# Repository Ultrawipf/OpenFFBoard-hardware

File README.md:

# OpenFFBoard-hardware
This contains the hardware designs of the OpenFFBoard

These are work in progress.
No guarantee for functionality or safety! The designs are experimental and may change at any time.
The firmware is available in the main [OpenFFBoard](https://github.com/Ultrawipf/OpenFFBoard) git.

This project requires soldering of many fine pitched parts including QFN. Availability of components may change over time so check for alternatives if something is not available.
The motor driver should be made with 2oz copper layers for best thermal performance!

The firmware may run on some third party development kits but as they have different pinouts and missing peripherals this is not recommended.

## Buy official kits
* [Elecrow](https://www.elecrow.com/open-ffboard-stm32f407-usb-interface-only.html)
* [Lectronz](https://www.lectronz.com/stores/gigawipf)
* [Tindie](https://www.tindie.com/stores/gigawipf/) or Discord.

Check the [Discord](https://discord.com/invite/gHtnEcP) and [project page](https://hackaday.io/project/163904-open-ffboard) for updates.

---

### LICENSE NOTE: The root license applies to all subfolders NOT containing their own LICENSE file. If a subfolder contains a different LICENSE file this different license applies to all subfolders below this LICENSE file.

**If you want to sell any hardware of this project yourself i would kindly ask you to get in contact with me ([mail](mailto:ffboard@y-richter.de) or Discord)**

## Changelog
### TMC Driver:

#### 1.1: (Prerelease prototype)
- Added filtering for Hall and Encoder inputs.
- Separated TMC and STM VM sense dividers

#### 1.2: (Major redesign)
- Using TMC4671-LA production version
- Added 5V buck converter
- Added emergency shutdown method by pulling enable low
- Rotated power stage. Moved all motor connectors to one side
- Moved analog encoder pins and routed differential inputs out
- Improved vcore impedance
- Increased encoder filter frequencies
- Reduced resistance of sense dividers
- Switched LM5050 to LM74700
- Space for 2 VM capacitors
- Improved mosfet protection
- Added temperature sensor pads on AGPI-B
- 50x50+100mm screw holes

#### 1.2 fix:
- Fixed silkscreen (R18 and R19 swapped)
- Modified some labels
- Added 33k gate pulldown for brake resistor
- Moved and resized vias in motor driver part (Manufacturing reliability)
- Tented vias

#### 1.2.2 (HALL):
- Redesigned power stage to use hall sensors (LEM GO SME and TMCS1100)
- Changed buffers to 74LV17APWJ
- Added opamp for TMC inputs (temperature and voltage sensing)
- Used opamp as comparator for hardware brake resistor activation point (~65V)
  
### 1.3.3:
- Analog section with separate LDO
- Support for more current sensors (ACS724)
- Optimized gate driver circuit w. resistors and diodes
- More separation between analog and power sections

### STM USB Interface:
#### 1.1:
- Initial prototype
- STM32F411RE based
- Only supports TMC4671 driver
- Only one SPI2 CS

#### 1.2:
- STM32F407VG
- Reserved PWM pins
- 3 CS pins per SPI
- CAN bus
- Reserved E-Stop
- USB Vbus sense
- separated ADCs for vsense and analog in
- LEDs moved
- Added FFBoard logo
- Changed USB diode to SMC
- Added zener pad on 5V
- Removed encoder buffer
- Higher value pwr led resistor

#### 1.2.1:
- Fixed some labels
- Moved USB socket and terminals slightly to the corners (Big usb plugs might interfere with the pins)
- Changed crystal load capacitors to lower values. (F407 DFU is very sensitive and does not work reliably with too high value caps)
- Added E-Stop capacitor against noise triggering it
- Tented vias

#### 1.2.2
- Swapped (Previously unused) Encoder Z pin from pin 65 to pin 62 because of interrupt conflicts with the DRV flag pin

#### 1.2.3
- USB-C instead of micro USB
- SPI1 uses a 2 row header
- Additional USB protections

#### 1.2.4
- Moved EXT header slightly
- Used 2 extra jumper pins for CAN termination instead of solderjumper

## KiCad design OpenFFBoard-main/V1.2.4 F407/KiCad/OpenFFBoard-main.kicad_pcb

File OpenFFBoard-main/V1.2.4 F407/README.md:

### FFBoard main USB interface F407VG
This is the heart of the Open FFBoard.
It runs the FFBoard firmware and interfaces with all your peripherals and motor drivers.

V1.2.3 and 1.2.4 is a USB-C version and adds additional USB protections.
The SPI1 port layout had to change to 2 rows instead of 1.

#### How to order yourself
You can order this board directly via [jlcpcb.com](https://jlcpcb.com/?from=Gigawipf).

The BOM and component placement files are available in the JLC assembly folder and already formatted with matching LCSC part numbers.

Everything apart from the headers can be directly assembled by JLC including the USB socket.

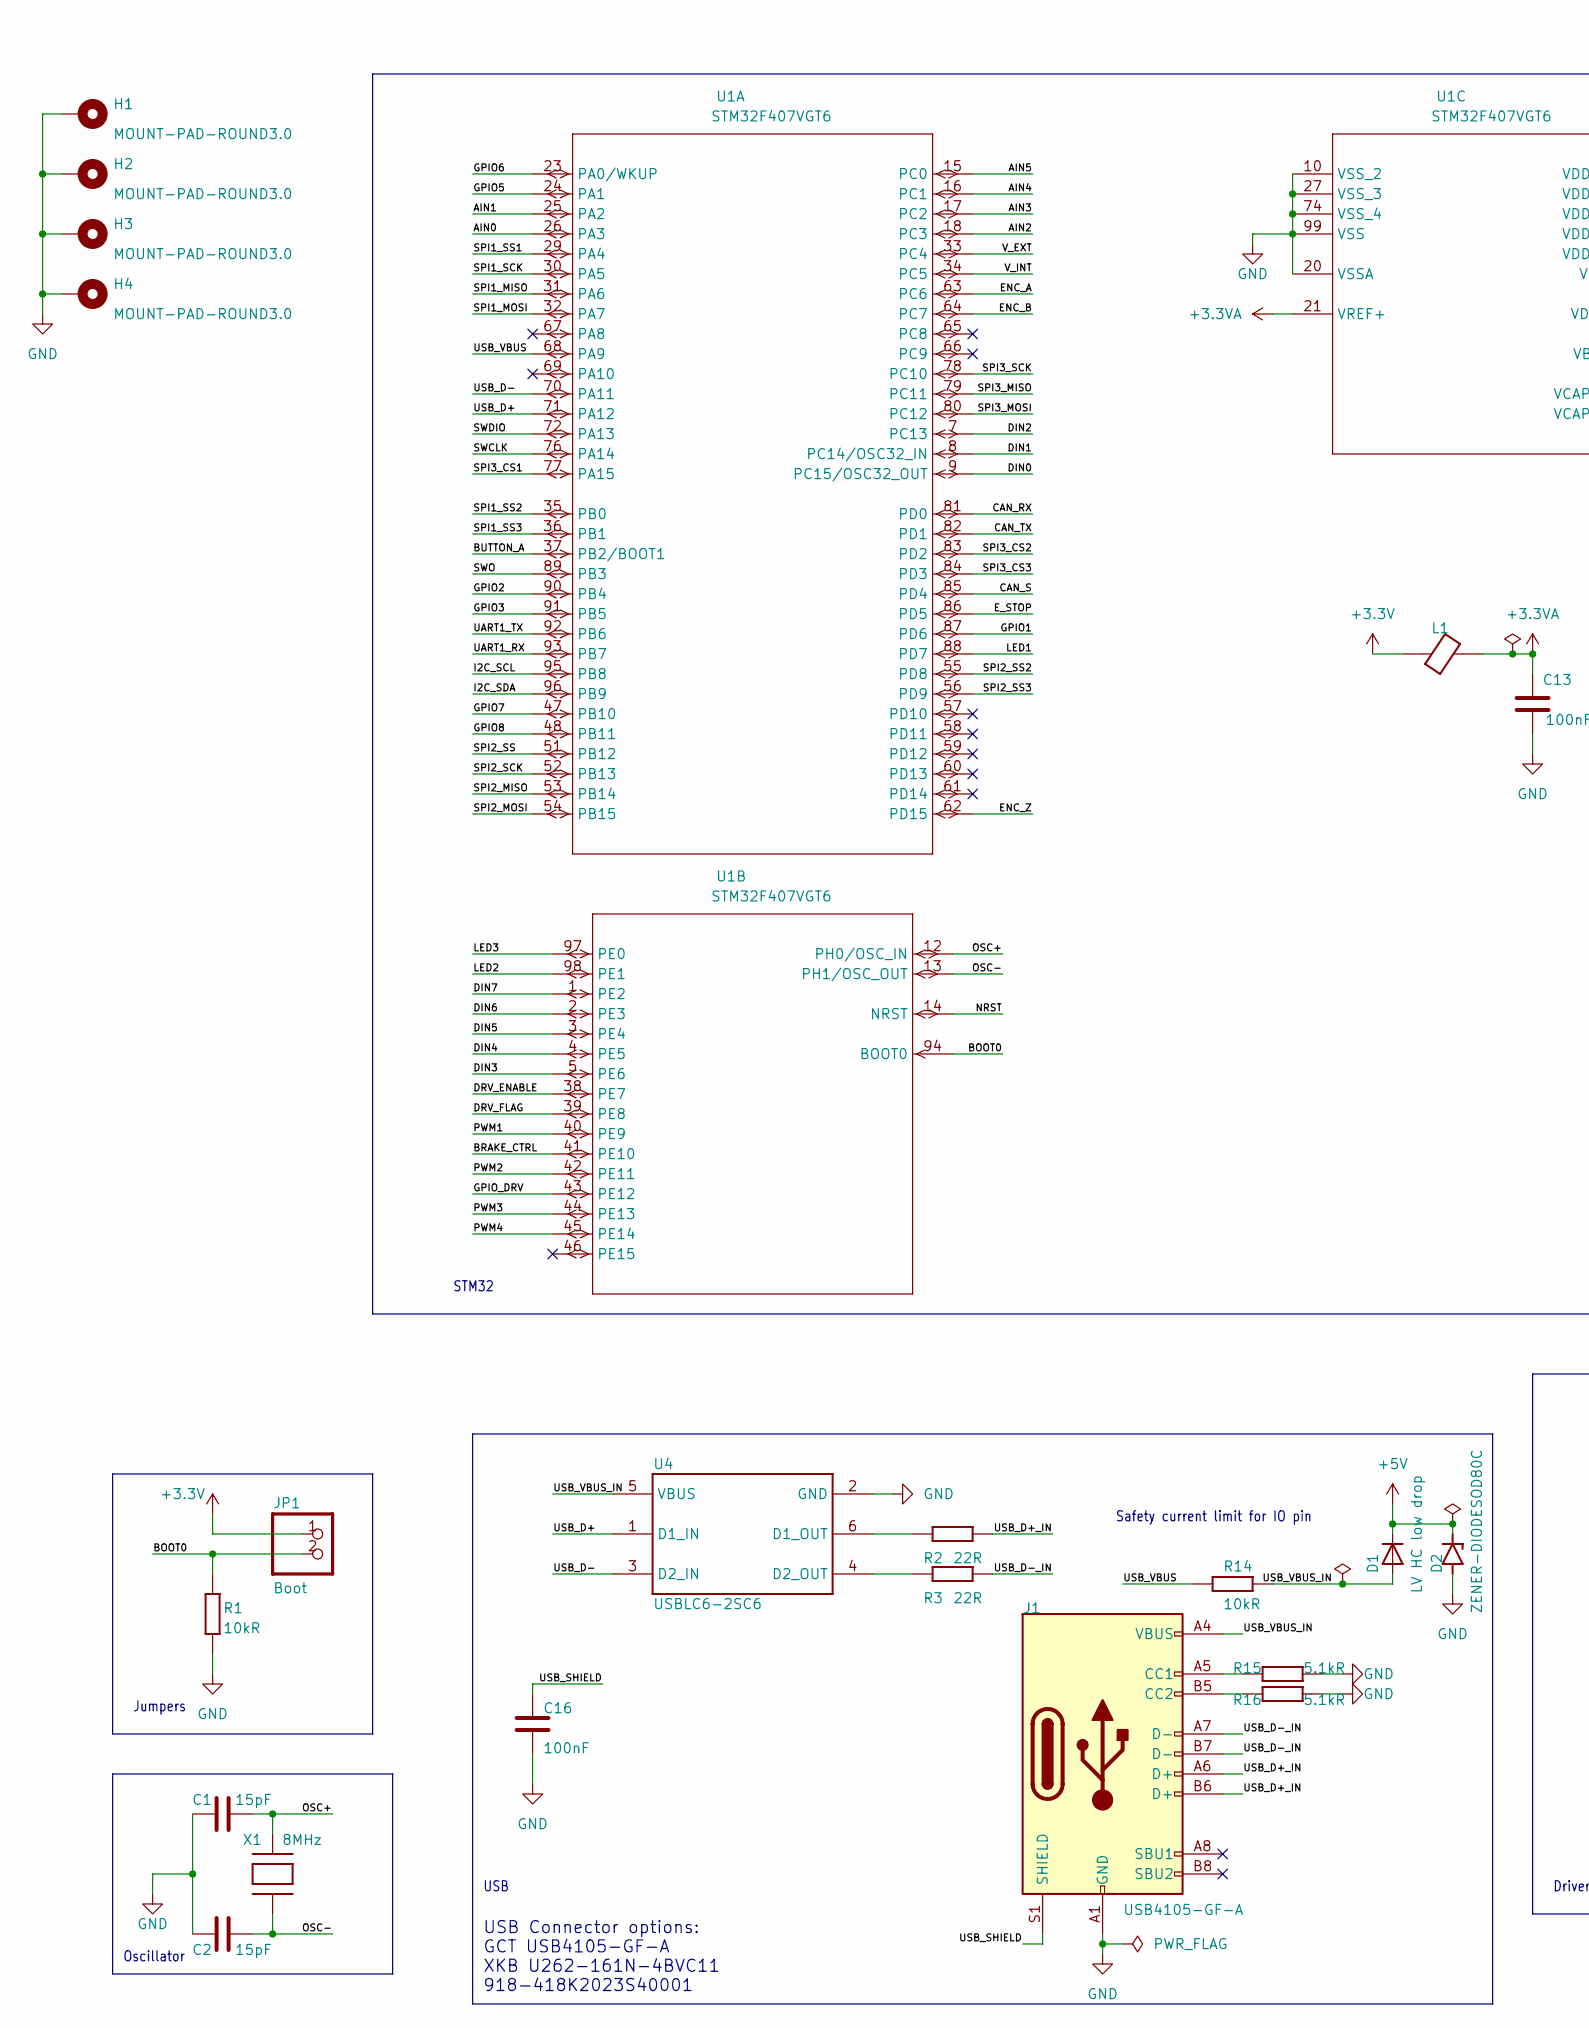
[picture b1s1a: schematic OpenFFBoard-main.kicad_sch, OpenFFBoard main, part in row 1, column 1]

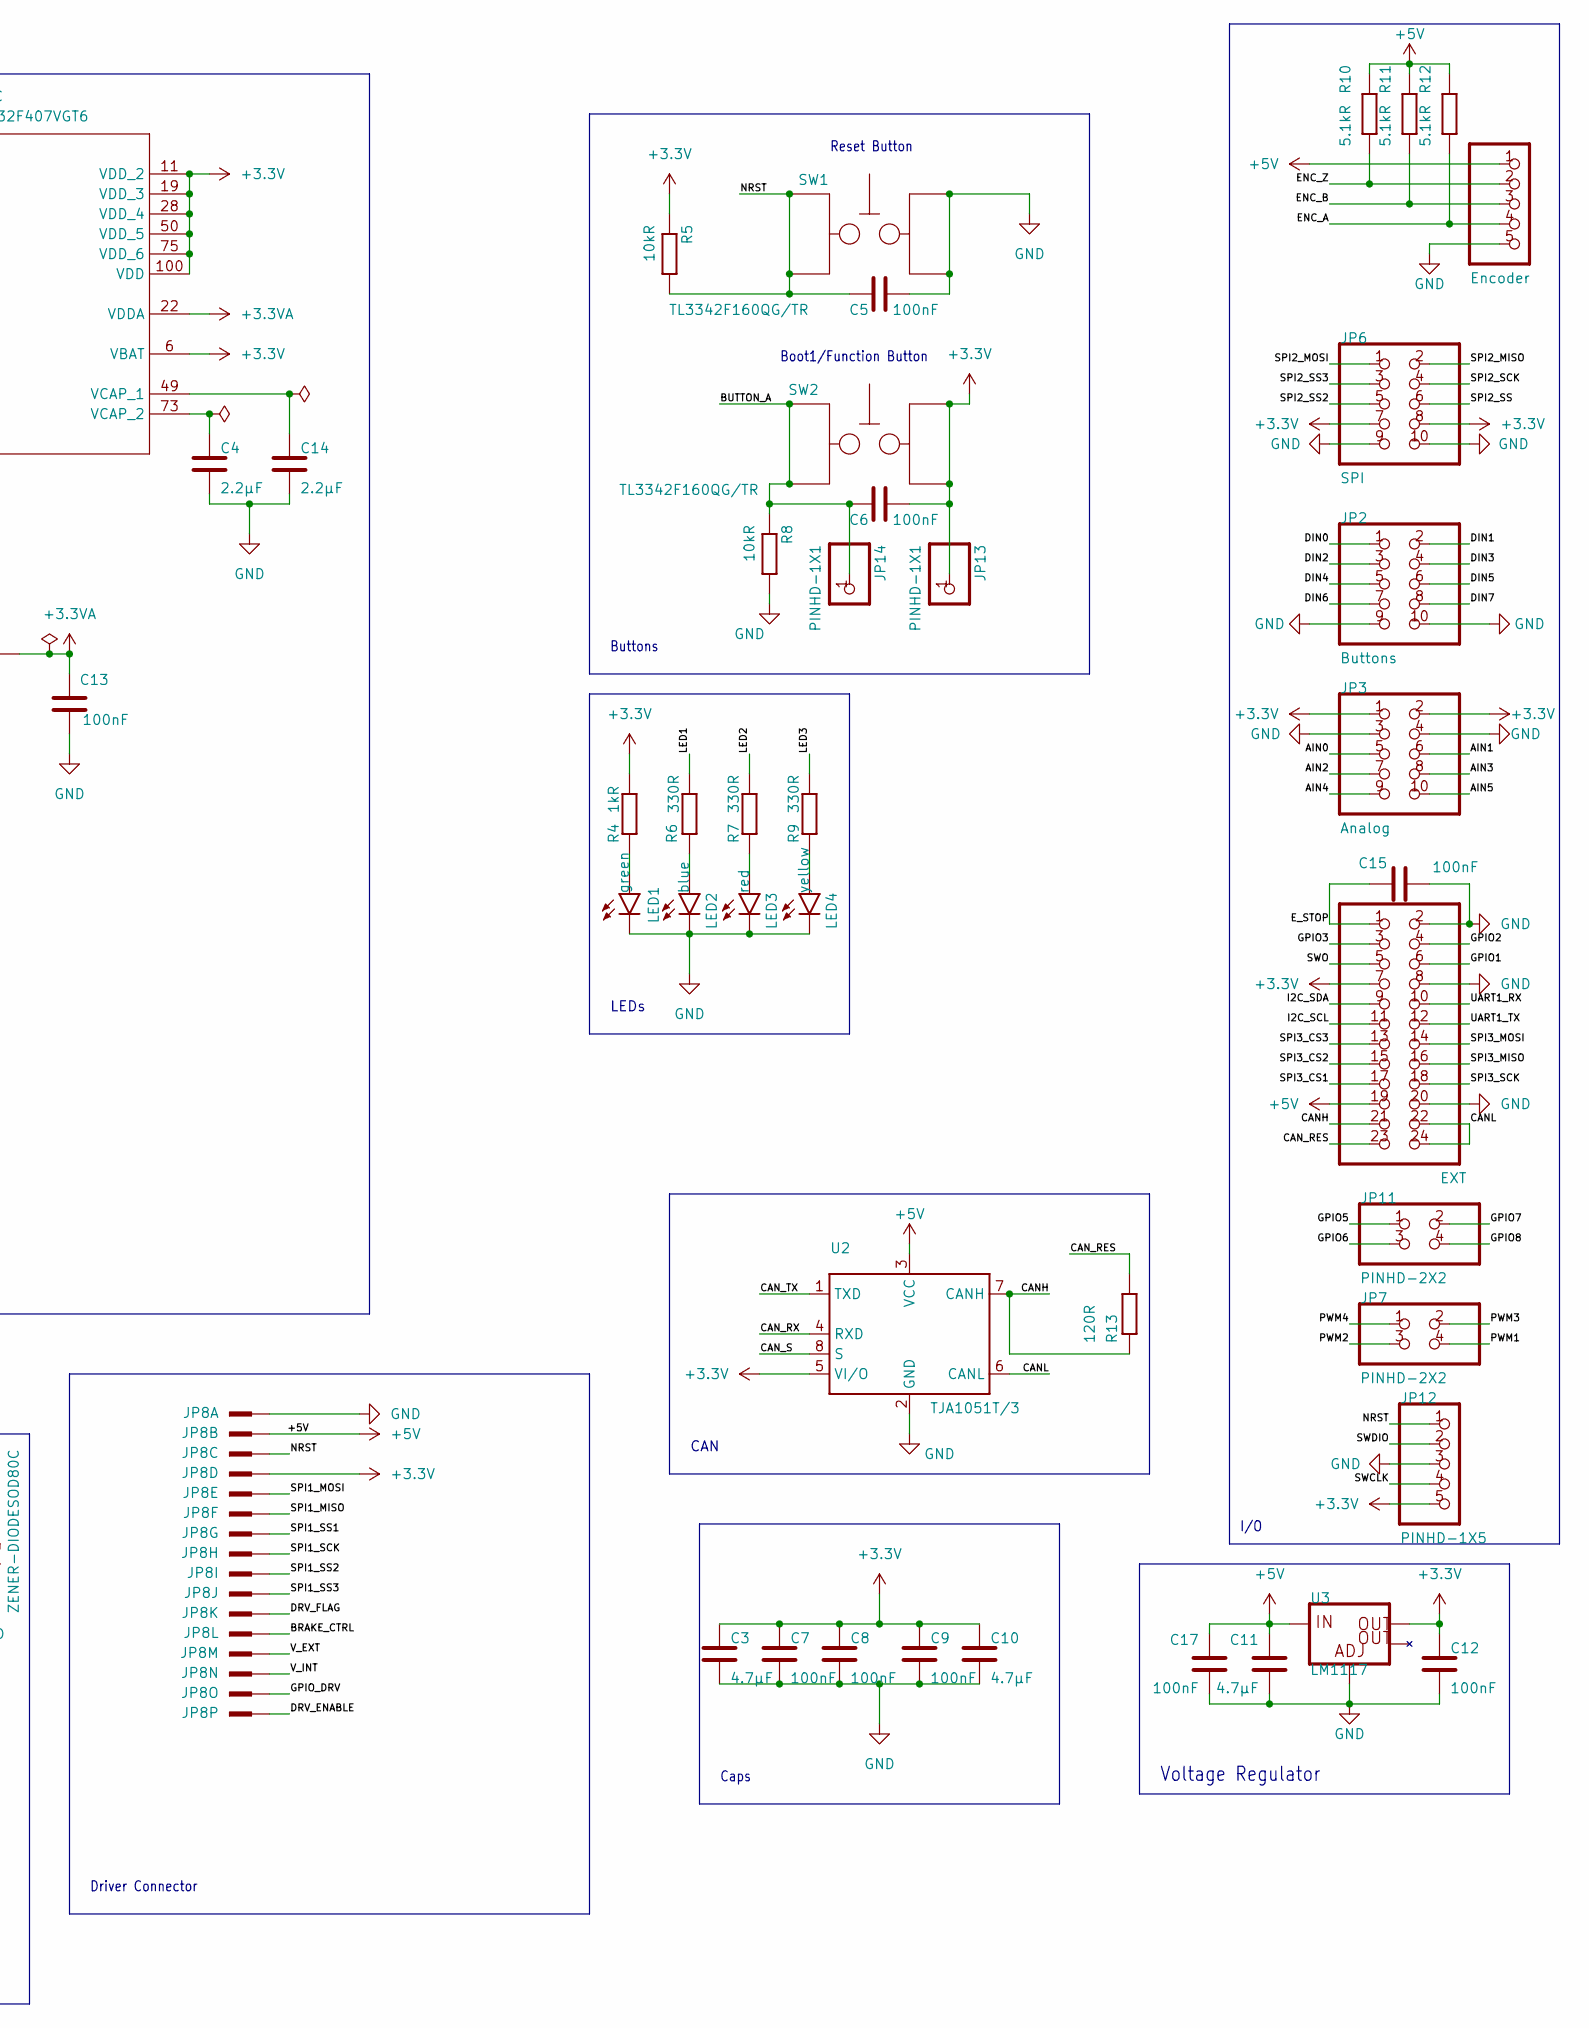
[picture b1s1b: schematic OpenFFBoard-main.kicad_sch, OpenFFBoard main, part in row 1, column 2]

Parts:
C1, C2: 15pF; C0603
C3, C10, C11: 4.7µF; C0805
C4, C14: 2.2µF; C0603
C5, C6, C7, C8, C9, C12, C13, C15, C16, C17: 100nF; C0603
D1: LV HC low drop; SMADIODE
D2: ZENER-DIODESOD80C; SOD80C
H1, H2, H3, H4: MOUNT-PAD-ROUND3.0; MountingHole_3.2mm_M3_Pad_Via
J1: USB4105-GF-A; GCT_USB4105-GF-A
JP1: Boot; 1X02
JP2: Buttons; 2X05
JP3: Analog; 2X05
JP4: EXT; 2X12
JP5: Encoder; 1X05
JP6: SPI; 2X05
JP7, JP11: PINHD-2X2; 2X02
JP8: 2516-; PAK100_2500-16
JP12: PINHD-1X5; 1X05
JP13, JP14: PINHD-1X1; 1X01
L1: GZ2012D601TF; BLM21PG331SN1D
LED1: green; SML0805
LED2: blue; SML0805
LED3: red; SML0805
LED4: yellow; SML0805
R1, R5, R8, R14: 10kR; R0603
R2, R3: 22R; R0603
R4: 1kR; R0603
R6, R7, R9: 330R; R0603
R10, R11, R12, R15, R16: 5.1kR; R0603
R13: 120R; R0603
SW1, SW2: TL3342F160QG/TR; TL3342F160QG_TR
U1: STM32F407VGT6; LQFP100-14X14MM
U2: TJA1051T/3; SOT96-1
U3: LM1117; SOT223
U4: USBLC6-2SC6; TSOT-23-6
X1: 8MHz; NX5032

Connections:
+3.3V: C3.1, C6.2, C7.1, C8.1, C9.1, C10.1, C12.1, JP1.1, JP3.1, JP3.2, JP4.7, JP6.7, JP6.8, JP8.4 (KL), JP12.5, JP13.1, L1.1, R4.2, R5.1, SW2.1, SW2.2, U1.6 (VBAT), U1.11 (VDD_2), U1.19 (VDD_3), U1.28 (VDD_4), U1.50 (VDD_5), U1.75 (VDD_6), U1.100 (VDD), U2.5 (VI/O), U3.4 (OUT)
+3.3VA: C13.2, L1.2, U1.21 (VREF+), U1.22 (VDDA)
+5V: C11.1, C17.2, D1.C, D2.C, JP4.19, JP5.1, JP8.2 (KL), R10.1, R11.1, R12.1, U2.3 (VCC), U3.3 (IN)
/AIN0: JP3.5, U1.26 (PA3)
/AIN1: JP3.6, U1.25 (PA2)
/AIN2: JP3.7, U1.18 (PC3)
/AIN3: JP3.8, U1.17 (PC2)
/AIN4: JP3.9, U1.16 (PC1)
/AIN5: JP3.10, U1.15 (PC0)
/BOOT0: JP1.2, R1.1, U1.94 (BOOT0)
/BRAKE_CTRL: JP8.12 (KL), U1.41 (PE10)
/BUTTON_A: C6.1, JP14.1, R8.1, SW2.3, SW2.4, U1.37 (PB2/BOOT1)
/CANH: JP4.21, R13.1, U2.7 (CANH)
/CANL: JP4.22, JP4.24, U2.6 (CANL)
/CAN_RES: JP4.23, R13.2
/CAN_RX: U1.81 (PD0), U2.4 (RXD)
/CAN_S: U1.85 (PD4), U2.8 (S)
/CAN_TX: U1.82 (PD1), U2.1 (TXD)
/DIN0: JP2.1, U1.9 (PC15/OSC32_OUT)
/DIN1: JP2.2, U1.8 (PC14/OSC32_IN)
/DIN2: JP2.3, U1.7 (PC13)
/DIN3: JP2.4, U1.5 (PE6)
/DIN4: JP2.5, U1.4 (PE5)
/DIN5: JP2.6, U1.3 (PE4)
/DIN6: JP2.7, U1.2 (PE3)
/DIN7: JP2.8, U1.1 (PE2)
/DRV_ENABLE: JP8.16 (KL), U1.38 (PE7)
/DRV_FLAG: JP8.11 (KL), U1.39 (PE8)
/ENC_A: JP5.4, R12.2, U1.63 (PC6)
/ENC_B: JP5.3, R11.2, U1.64 (PC7)
/ENC_Z: JP5.2, R10.2, U1.62 (PD15)
/E_STOP: C15.1, JP4.1, U1.86 (PD5)
/GPIO1: JP4.6, U1.87 (PD6)
/GPIO2: JP4.4, U1.90 (PB4)
/GPIO3: JP4.3, U1.91 (PB5)
/GPIO5: JP11.1, U1.24 (PA1)
/GPIO6: JP11.3, U1.23 (PA0/WKUP)
/GPIO7: JP11.2, U1.47 (PB10)
/GPIO8: JP11.4, U1.48 (PB11)
/GPIO_DRV: JP8.15 (KL), U1.43 (PE12)
/I2C_SCL: JP4.11, U1.95 (PB8)
/I2C_SDA: JP4.9, U1.96 (PB9)
/LED1: R6.2, U1.88 (PD7)
/LED2: R7.2, U1.98 (PE1)
/LED3: R9.2, U1.97 (PE0)
/NRST: C5.1, JP8.3 (KL), JP12.1, R5.2, SW1.3, SW1.4, U1.14 (NRST)
/OSC+: C1.2, U1.12 (PH0/OSC_IN), X1.P$2
/OSC-: C2.2, U1.13 (PH1/OSC_OUT), X1.P$1
/PWM1: JP7.4, U1.40 (PE9)
/PWM2: JP7.3, U1.42 (PE11)
/PWM3: JP7.2, U1.44 (PE13)
/PWM4: JP7.1, U1.45 (PE14)
/SPI1_MISO: JP8.6 (KL), U1.31 (PA6)
/SPI1_MOSI: JP8.5 (KL), U1.32 (PA7)
/SPI1_SCK: JP8.8 (KL), U1.30 (PA5)
/SPI1_SS1: JP8.7 (KL), U1.29 (PA4)
/SPI1_SS2: JP8.9 (KL), U1.35 (PB0)
/SPI1_SS3: JP8.10 (KL), U1.36 (PB1)
/SPI2_MISO: JP6.2, U1.53 (PB14)
/SPI2_MOSI: JP6.1, U1.54 (PB15)
/SPI2_SCK: JP6.4, U1.52 (PB13)
/SPI2_SS: JP6.6, U1.51 (PB12)
/SPI2_SS2: JP6.5, U1.55 (PD8)
/SPI2_SS3: JP6.3, U1.56 (PD9)
/SPI3_CS1: JP4.17, U1.77 (PA15)
/SPI3_CS2: JP4.15, U1.83 (PD2)
/SPI3_CS3: JP4.13, U1.84 (PD3)
/SPI3_MISO: JP4.16, U1.79 (PC11)
/SPI3_MOSI: JP4.14, U1.80 (PC12)
/SPI3_SCK: JP4.18, U1.78 (PC10)
/SWCLK: JP12.4, U1.76 (PA14)
/SWDIO: JP12.2, U1.72 (PA13)
/SWO: JP4.5, U1.89 (PB3)
/UART1_RX: JP4.10, U1.93 (PB7)
/UART1_TX: JP4.12, U1.92 (PB6)
/USB_D+: U1.71 (PA12), U4.1 (D1_IN)
/USB_D+_IN: J1.A6 (D+), J1.B6 (D+), R2.2
/USB_D-: U1.70 (PA11), U4.3 (D2_IN)
/USB_D-_IN: J1.A7 (D-), J1.B7 (D-), R3.2
/USB_SHIELD: C16.1, J1.S1 (SHIELD)
/USB_VBUS: R14.1, U1.68 (PA9)
/USB_VBUS_IN: D1.A, J1.A4 (VBUS), J1.A9 (VBUS), J1.B4 (VBUS), J1.B9 (VBUS), R14.2, U4.5 (VBUS)
/V_EXT: JP8.13 (KL), U1.33 (PC4)
/V_INT: JP8.14 (KL), U1.34 (PC5)
GND: C1.1, C2.1, C3.2, C4.2, C5.2, C7.2, C8.2, C9.2, C10.2, C11.2, C12.2, C13.1, C14.2, C15.2, C16.2, C17.1, D2.A, H1.1, H2.1, H3.1, H4.1, J1.A1 (GND), J1.A12 (GND), J1.B1 (GND), J1.B12 (GND), JP2.9, JP2.10, JP3.3, JP3.4, JP4.2, JP4.8, JP4.20, JP5.5, JP6.9, JP6.10, JP8.1 (KL), JP12.3, LED1.C, LED2.C, LED3.C, LED4.C, R1.2, R8.2, R15.1, R16.2, SW1.1, SW1.2, U1.10 (VSS_2), U1.20 (VSSA), U1.27 (VSS_3), U1.74 (VSS_4), U1.99 (VSS), U2.2 (GND), U3.1 (ADJ), U4.2 (GND)
unnamed: C4.1, U1.73 (VCAP_2)
unnamed: C14.1, U1.49 (VCAP_1)
unnamed: J1.A5 (CC1), R15.2
unnamed: J1.B5 (CC2), R16.1
unnamed: LED1.A, R4.1
unnamed: LED2.A, R6.1
unnamed: LED3.A, R7.1
unnamed: LED4.A, R9.1
unnamed: R2.1, U4.6 (D1_OUT)
unnamed: R3.1, U4.4 (D2_OUT)

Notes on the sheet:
Safety current limit for IO pin
Voltage Regulator
USB Connector options: GCT USB4105-GF-A XKB U262-161N-4BVC11 918-418K2023S40001
I/O
Jumpers
CAN
Reset Button
Driver Connector
Oscillator
Buttons
Boot1/Function Button
USB
Caps
LEDs
STM32

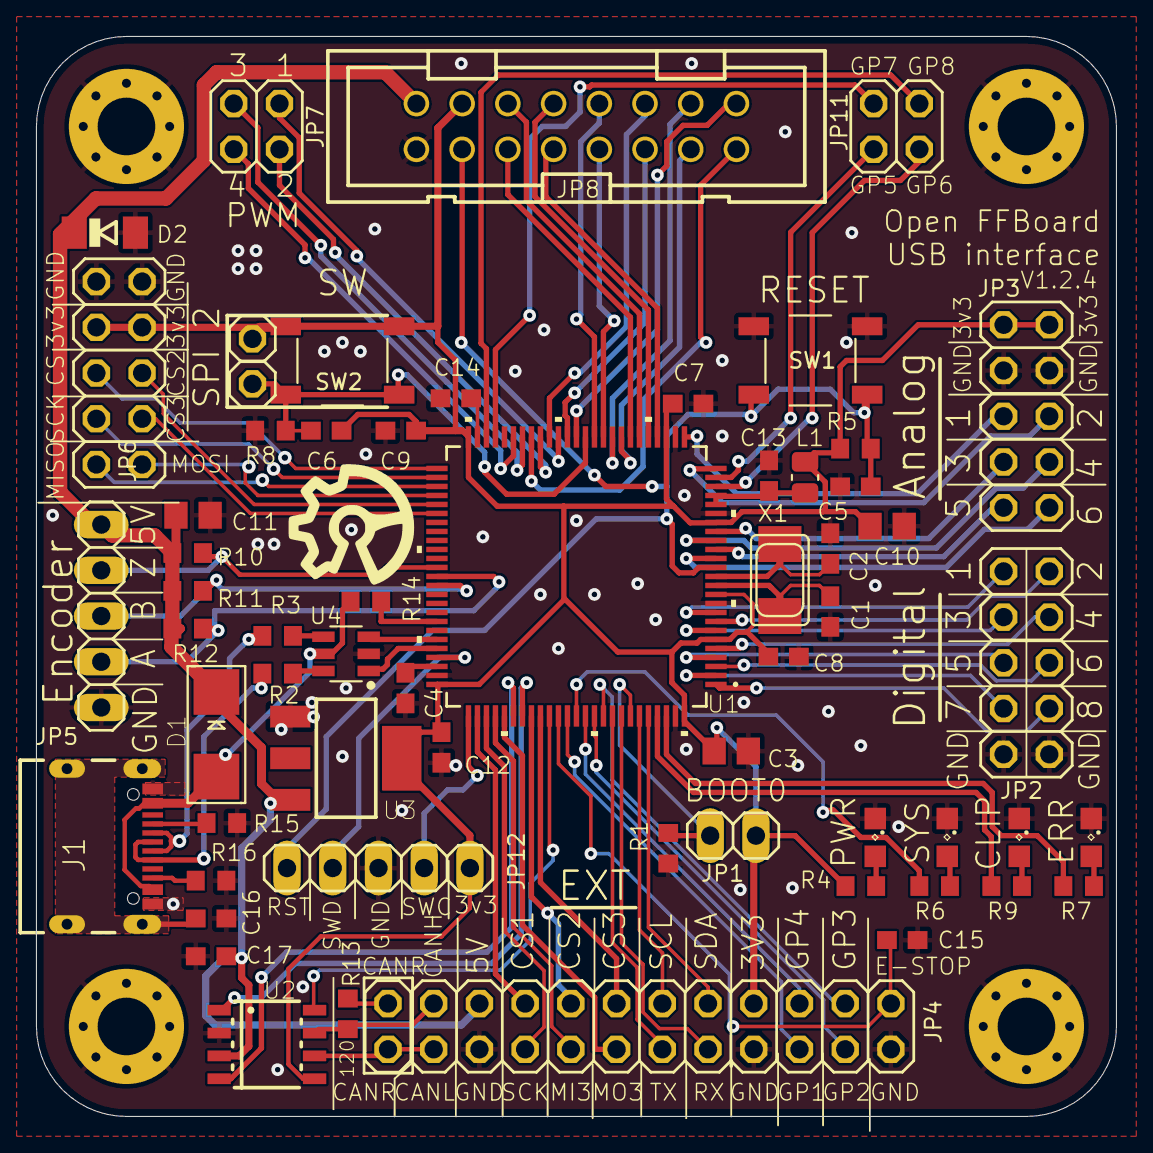
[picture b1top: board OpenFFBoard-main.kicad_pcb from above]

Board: 2 copper layers, 60.0 x 60.0 mm, 64 parts (0 on the bottom side), 95 nets.

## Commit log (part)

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2020-03-21 Added TMC driver
2020-04-16 Changing clearances to 8 mil and renamed shunt amps
2020-08-17 Updated TMC4671 board to redesigned 1.2 version.
2020-09-19 Added 1.1.1 stm board
2020-10-19 Edited readme formatting
2020-10-19 Improved readme formatting
2020-10-19 Improved readme formatting (#1)
    Improved readme formatting
2020-10-22 Updated TMC Board. Fixed D12 value
2020-11-13 Updated STM Board to v1.2
2020-11-14 Fixed swapped PWM channel labels
2020-11-14 Added E-Stop cap
2020-12-06 Updated crystal capacitor value
2021-01-08 Fixed swapped sense resistor labels in BOM for TMC
2021-01-09 Update README.md
    fixed links
2021-01-10 Fixed tmc silkscreen (Resistor names, labels)
2021-02-11 Added F407 board schematic pdf
2021-04-18 Swapped encoder Z pin on F407 board
2021-09-26 Schematic for f407 updated
2021-12-13 Added load cell amplifier files
2022-01-14 Added files for Hall sensor TMC
2022-06-02 Added USB-C V1.2.3 ffboard
2022-06-23 Fixed error in TMC V1.2 bom
2022-06-23 Added 32 button SPI input module design files
2022-06-23 Added SPI buttons readme
2022-08-14 Removed C27 and C28 from BOM
2022-08-14 Added F407 V1.2.4 files
2022-08-17 Added mention of max5033busa
2022-08-31 Readme update
2022-11-25 Updated BOM for TMC V1.2.2 hall and STM V1.2.4
2022-12-29 Ported project from EAGLE to KiCad
    Minimal port with only the necessary changes to pass ERC and DRC.
2022-12-29 Moved kicad port folder inside 1.2.4 folder
2022-12-31 Cosmetic changes on silkscreen. No more warnings
2022-12-31 Added missing logo
2022-12-31 Consistent naming convention and font size on schematic
2022-12-31 Updated design constraints
2023-01-02 Generated manufacturing files
2023-02-11 SPI button update
2023-02-11 Added BISS-C adapter
2023-02-13 License update to subfolder
2023-04-03 Made F407 pin1 marker more visible
2023-07-16 Renamed CLIP LED to FFB
2023-07-26 Updated links
2023-07-26 Replaces 2.2r with 22r in v1.2.2 tmc
2023-09-16 Added TMC 1.3.3 version
2025-03-03 Updated SPI buttons to v1.2
2025-03-03 Added lasercut case
2025-04-10 Added F407 1.2.4 3D models
